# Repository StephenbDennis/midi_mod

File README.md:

# Github Pages
https://stephenbdennis.github.io/midi_mod/

# Modular USB MIDI Controller (Midi-Mod)

A **USB MIDI device** that supports up to **3 hot-swappable input modules**, configurable as **buttons**, **sliders**, or **potentiometers**.  
I was going for a compact design that allowed the user to configure their Midi-Mod device without needing firmware updates.
* Note: This is a work in progress... It's working, but there are many things that could be improved.

---

## Configure it in a browser

**[stephenbdennis.github.io/midi_mod](https://stephenbdennis.github.io/midi_mod/)**

Pick a message for every input and watch the MIDI bytes it will put on the wire. There is a preset
per module type (Buttons, Sliders, Pots), it imports a config you already have, and it can listen to
the device over Web MIDI so you can check what it is actually sending. Everything runs in the
browser; nothing is uploaded.

**Connect** pairs with the device over Bluetooth. From there **Load from device** pulls the config
that is on it right now, and **Send to device** writes `config.toml` back and applies it
immediately &mdash; no replug, and the device stays a USB MIDI interface throughout, so you can keep
playing into a DAW while you edit. Transfers are checksummed in both directions and rejected if they
do not match.

Bluetooth needs Web Bluetooth, so it is Chrome, Edge and Opera only (on Linux you may have to enable
it in `chrome://flags`). Everywhere else, Download still gives you the same `config.toml`.

---

### Project Build and Flash

Needs **ESP-IDF 5.2 or newer**. Dependencies come from `dependencies.lock`; `idf.py` fetches them
on the first build.

```
idf.py set-target esp32s3
idf.py build
idf.py -p COM<xxx> flash
idf.py -p COM<xxx> monitor
```

---

## Features

- **Up to 3 modules active at once**
- Modules can be:
  - Button Module (5 Cherry Mx buttons)
  - Slider Module (2 Linear Potentiometers)
  - Pot Module (5 Knob Potentiometers)
- Modules can be **mixed** (e.g. 3 Button Modules or 1 Button + 1 Slider + 1 Pot)
- **Every MIDI message**: notes, aftertouch, control change, program change, pitch bend, and the
  system common and real time messages
- Configurable with onboard .toml(ish) file
- BLE config service, so it can be reconfigured while it plays

---

## Module Types

Each module occupies **one slot**.  
A maximum of **3 slots** are available.

### 1. Button Module
- Defaults to a digital device when connected

### 2. Slider Module
- Defaults to an analog device when connected
- Uses dual sliders, so device 1 and 2 should have the roughly the same value. and well as 3 and 4. Device 5 is tied to ground.

### 3. Potentiometer Module
- Defaults to an analog device when connected

---

## Configuration
- The device advertises over Bluetooth LE as **MIDI-Mod** whenever it is powered. Open the
  configurator, press Connect, and pick it from the browser's device chooser. There is no config
  boot mode any more: USB is the MIDI interface full time.

- **Send to device** writes `config.toml` into the device's internal filesystem and applies it on
  the next poll tick, so a change is audible straight away.

- `reference.txt` is written to the internal filesystem on first boot. It documents the config
  format, though the same reference is on the configurator page under **Message reference**.

- If no config.toml is present the device writes the example below, so there is always something to edit.

- A line starting with `#` is a comment. Numbers are hexadecimal.

### Module Options
- press_velocity : (Optional) 0x0-0x7F : Defaults to 0x7F
  - This is the note_on/note_off message velocity. Only used with buttons
- channel 	     : (Optional) 0x0-0xF  : Defaults to 0x0
  - The channel messages are sent on. (Part of the MIDI message)
- alpha	    	 : (Optional) 0.01-0.5 : Defaults to 0.3
  - This value changes the responsivity of the input. Higher is faster, Lower is smoother but slower. Currently buttons are analog reads, so this should be pretty high when using that module
### Device Options
- device_type          : (Optional) analog,digital                 : Defaults to module type
  - Digital: triggers message_on_change on the rising edge and message_on_stop on the falling edge. 
  - Analog:  triggers message_on_change when value is changing and message_on_stop when the value is no longer changing. 
- channel              : (Optional) 0x0-0xF,inherit                : Defaults to inherit
  - Overrides the module channel for this one input. System messages ignore it.
- message_on_change    : (Optional) see Messages below             : Defaults to noop
  - The message to send when the value changes (analog) or rising edge (digital). This can be a name or a status byte
- message_on_stop      : (Optional) see Messages below             : Defaults to noop
  - The message to send when the value stops changing (analog) or falling edge (digital). This can be a name or a status byte
- data 	               : (Optional) notes,0x0-0x7F                 : Defaults to 0x0. 
  - For messages that carry a note, controller or program number this will be the value in the message. This can be a note string or a hex value. Overwritten by Manual Data
- manual_data_change_0 : (Optional) 0x0-0x7F,dev                   : Not used if not set
  - If set this will set the first data byte on a change action to this value. If dev, the value of the device is used 
- manual_data_change_1 : (Optional) 0x0-0x7F,dev                   : Not used if not set
  - If set this will set the second data byte on a change action to this value. If dev, the value of the device is used
- manual_data_stop_0   : (Optional) 0x0-0x7F,dev                   : Not used if not set
  - If set this will set the first data byte on a stop action to this value. If dev, the value of the device is used
- manual_data_stop_1   : (Optional) 0x0-0x7F,dev                   : Not used if not set
  - If set this will set the second data byte on a stop action to this value. If dev, the value of the device is used

### Messages

`input` is the live 0-127 reading of the button, slider or knob. `data` is the device's `data` option.

| Name | Status | Bytes | Data 1 | Data 2 |
| --- | --- | --- | --- | --- |
| `noop` | - | 0 | nothing is sent | |
| `note_off` | 0x80 | 3 | note (data) | velocity (press_velocity) |
| `note_on` | 0x90 | 3 | note (data) | velocity (press_velocity) |
| `poly_aftertouch` | 0xA0 | 3 | note (data) | pressure (input) |
| `cc` | 0xB0 | 3 | controller (data) | value (input) |
| `pc` | 0xC0 | 2 | program (data) | |
| `channel_aftertouch` | 0xD0 | 2 | pressure (input) | |
| `pitch_bend` | 0xE0 | 3 | bend LSB (input) | bend MSB (input) |
| `mtc_quarter_frame` | 0xF1 | 2 | time code (data) | |
| `song_position` | 0xF2 | 3 | position LSB (input) | position MSB (input) |
| `song_select` | 0xF3 | 2 | song (data) | |
| `tune_request` | 0xF6 | 1 | | |
| `clock` | 0xF8 | 1 | | |
| `start` | 0xFA | 1 | | |
| `continue` | 0xFB | 1 | | |
| `stop` | 0xFC | 1 | | |
| `active_sensing` | 0xFE | 1 | | |
| `system_reset` | 0xFF | 1 | | |

- Aliases: `control_change` = `cc`, `program_change` = `pc`, `channel_pressure` = `channel_aftertouch`, `timing_clock` = `clock`
- A raw status byte such as `0x90` works in place of a name
- Messages from 0xF1 up are system messages and ignore the channel
- `pitch_bend` and `song_position` spread the 0-127 reading across their full 14 bit range

### Notes
`C_(-1..9)` `C#_(-1..9)` `D_(-1..9)` `D#_(-1..9)` `E_(-1..9)` `F_(-1..9)` `F#_(-1..9)` `G_(-1..9)` `G#_(-1..8)` `A_(-1..8)` `A#_(-1..8)` `B_(-1..8)`

### Example
```
[module1]
channel = 0x0
press_velocity = 0x7F
alpha = 0.5
[module1.device1]
message_on_change = note_on
message_on_stop = note_off
data = C_3
[module1.device2]
message_on_change = note_on
message_on_stop = note_off
data = D_3
[module1.device3]
message_on_change = note_on
message_on_stop = note_off
data = E_3
[module1.device4]
message_on_change = start
message_on_stop = stop
[module1.device5]
message_on_change = pc
data = 0x0

[module2]
channel = 0x0
alpha = 0.3
[module2.device1]
message_on_change = cc
data = 0x1
[module2.device2]
message_on_change = cc
data = 0x7
[module2.device3]
message_on_change = cc
data = 0xA
[module2.device4]
message_on_change = pitch_bend
[module2.device5]
message_on_change = channel_aftertouch

[module3]
channel = 0x1
alpha = 0.3
[module3.device1]
message_on_change = cc
data = 0x0
[module3.device2]
message_on_change = cc
data = 0x2
[module3.device3]
message_on_change = poly_aftertouch
data = C_3
[module3.device4]
message_on_change = cc
data = 0x4
[module3.device5]
message_on_change = cc
data = 0x5
```

---

## Repo layout

| Path | What it is |
| --- | --- |
| `main/` | ESP32-S3 firmware |
| `boards/` | KiCad projects for the main board and the three module types |
| `docs/` | The web configurator, published to GitHub Pages |
| `.github/workflows/pages.yml` | Deploys `docs/` on every push to `main` |

To turn the page on, set **Settings → Pages → Source** to **GitHub Actions**. (Deploying from the
`main` branch `/docs` folder works too, and needs no workflow.)

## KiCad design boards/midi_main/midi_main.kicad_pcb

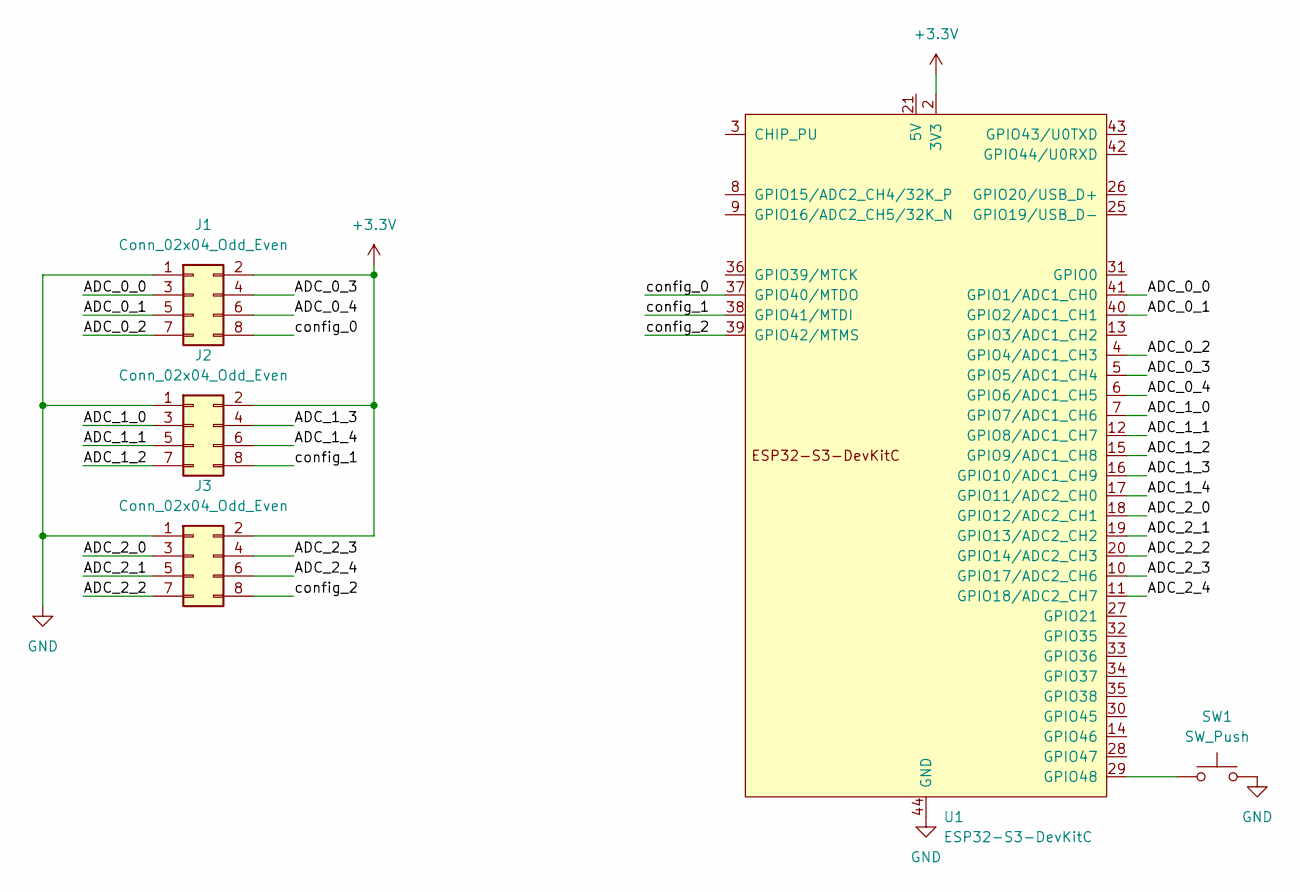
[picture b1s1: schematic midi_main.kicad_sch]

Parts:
J1, J2, J3: Conn_02x04_Odd_Even; MidiModuleOutline
SW1: SW_Push; SW_PUSH_6mm_H7.3mm
U1: ESP32-S3-DevKitC; ESP32-S3-DevKitC_Steve

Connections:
+3.3V: J1.2, J2.2, J3.2, U1.1 (3V3), U1.2 (3V3)
/ADC_0_0: J1.3, U1.41 (GPIO1/ADC1_CH0)
/ADC_0_1: J1.5, U1.40 (GPIO2/ADC1_CH1)
/ADC_0_2: J1.7, U1.4 (GPIO4/ADC1_CH3)
/ADC_0_3: J1.4, U1.5 (GPIO5/ADC1_CH4)
/ADC_0_4: J1.6, U1.6 (GPIO6/ADC1_CH5)
/ADC_1_0: J2.3, U1.7 (GPIO7/ADC1_CH6)
/ADC_1_1: J2.5, U1.12 (GPIO8/ADC1_CH7)
/ADC_1_2: J2.7, U1.15 (GPIO9/ADC1_CH8)
/ADC_1_3: J2.4, U1.16 (GPIO10/ADC1_CH9)
/ADC_1_4: J2.6, U1.17 (GPIO11/ADC2_CH0)
/ADC_2_0: J3.3, U1.18 (GPIO12/ADC2_CH1)
/ADC_2_1: J3.5, U1.19 (GPIO13/ADC2_CH2)
/ADC_2_2: J3.7, U1.20 (GPIO14/ADC2_CH3)
/ADC_2_3: J3.4, U1.10 (GPIO17/ADC2_CH6)
/ADC_2_4: J3.6, U1.11 (GPIO18/ADC2_CH7)
/config_0: J1.8, U1.37 (GPIO40/MTDO)
/config_1: J2.8, U1.38 (GPIO41/MTDI)
/config_2: J3.8, U1.39 (GPIO42/MTMS)
GND: J1.1, J2.1, J3.1, SW1.2, U1.22 (GND), U1.23 (GND), U1.24 (GND), U1.44 (GND)
unnamed: SW1.1, U1.29 (GPIO48)

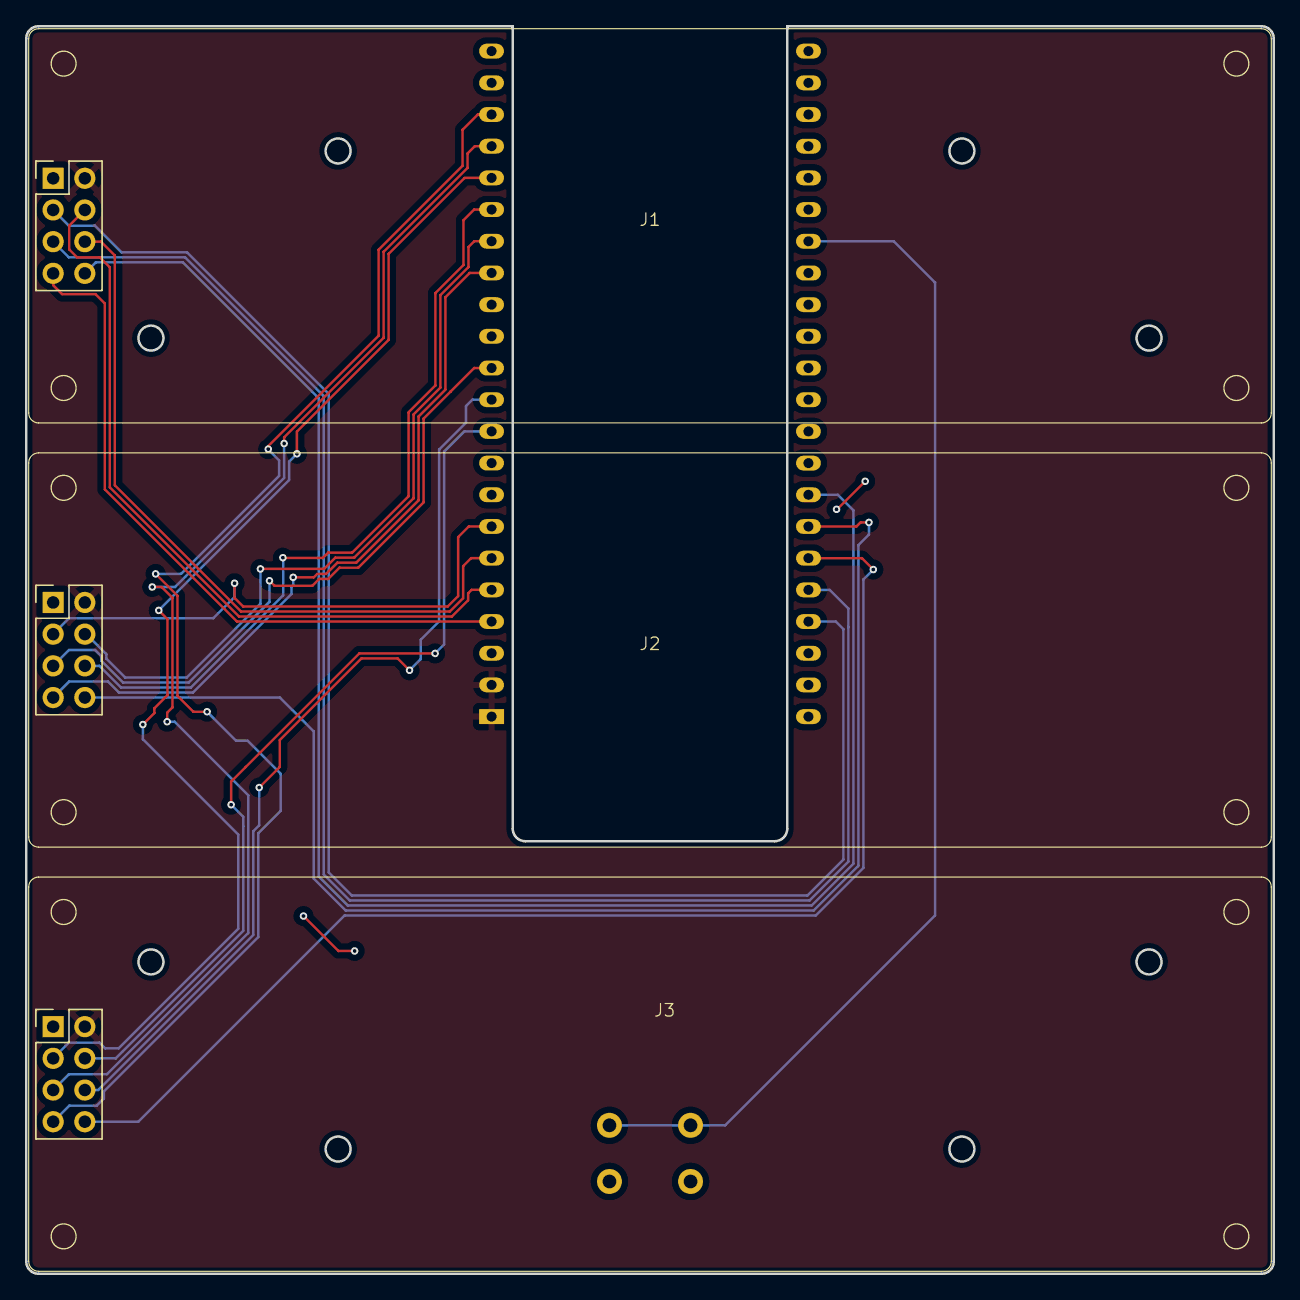
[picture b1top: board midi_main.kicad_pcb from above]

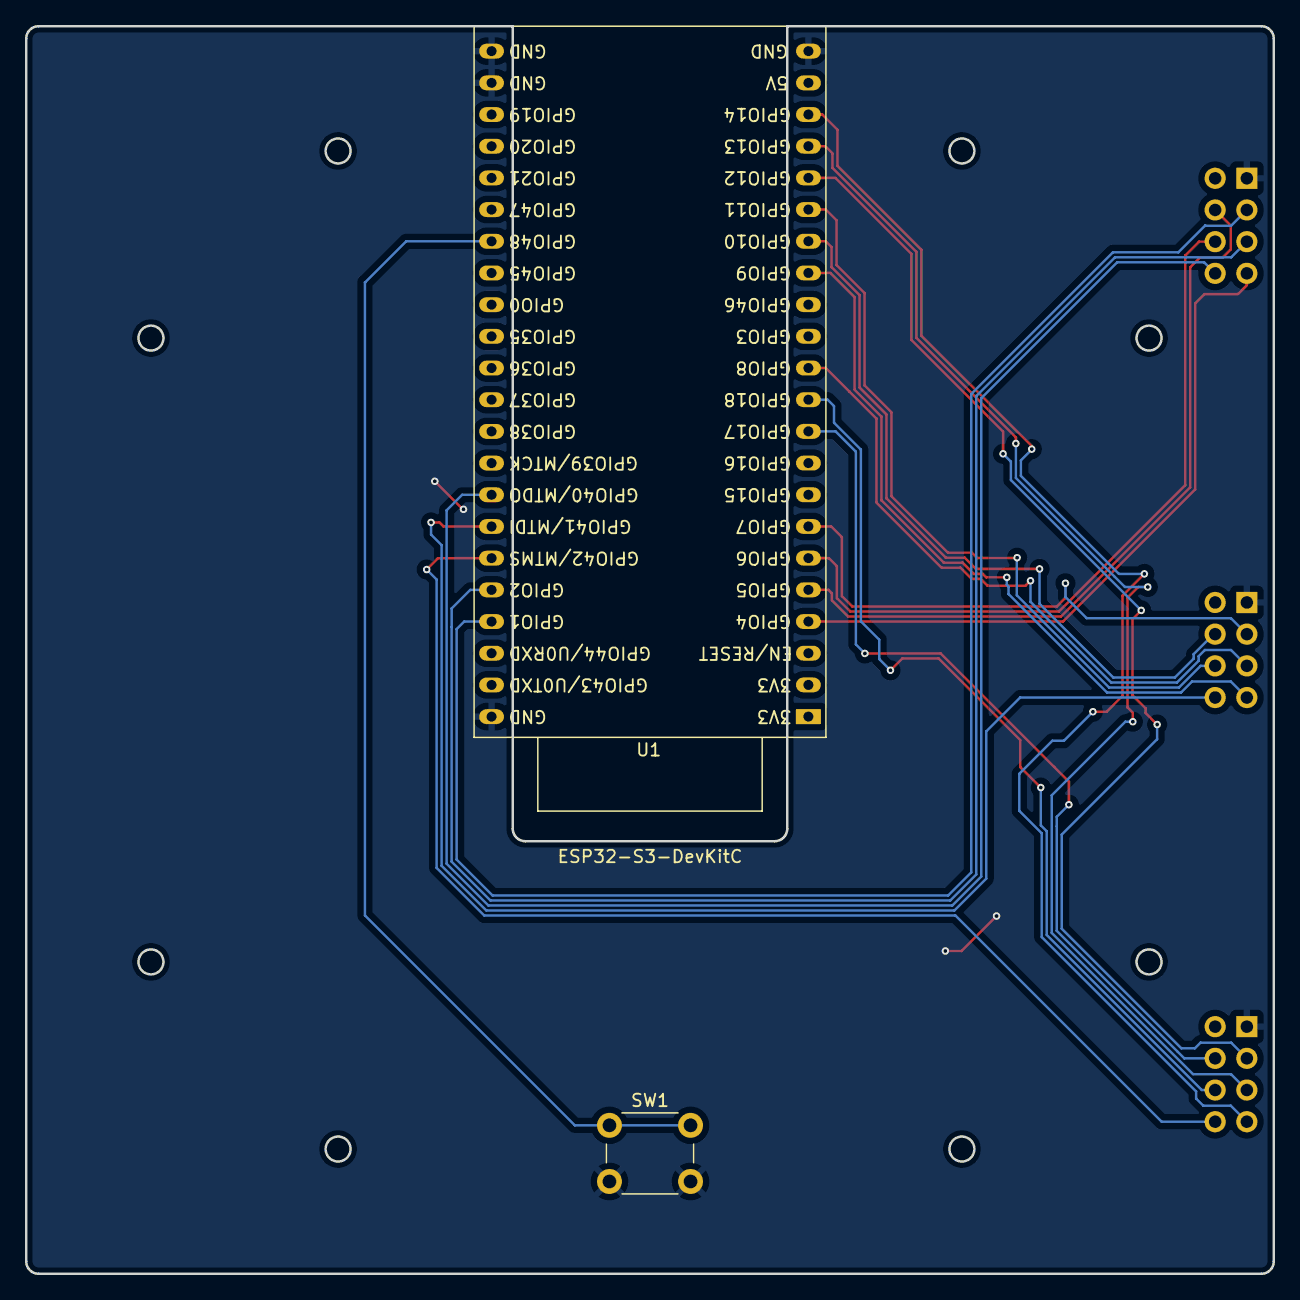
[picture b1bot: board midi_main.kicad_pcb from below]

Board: 2 copper layers, 100.0 x 100.0 mm, 5 parts (2 on the bottom side), 21 nets.

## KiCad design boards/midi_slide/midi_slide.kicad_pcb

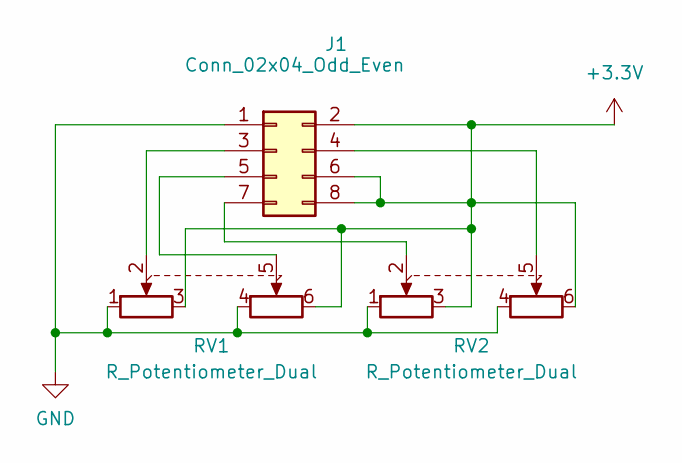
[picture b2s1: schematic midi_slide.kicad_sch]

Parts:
J1: Conn_02x04_Odd_Even; MidiModuleBase
RV1, RV2: R_Potentiometer_Dual; PS60M-0MC2BR10KN

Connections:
+3.3V: J1.2, J1.6, J1.8, RV1.3, RV1.6, RV2.3, RV2.6
GND: J1.1, RV1.1, RV1.4, RV2.1, RV2.4
unnamed: J1.3, RV1.2
unnamed: J1.4, RV2.5
unnamed: J1.5, RV1.5
unnamed: J1.7, RV2.2

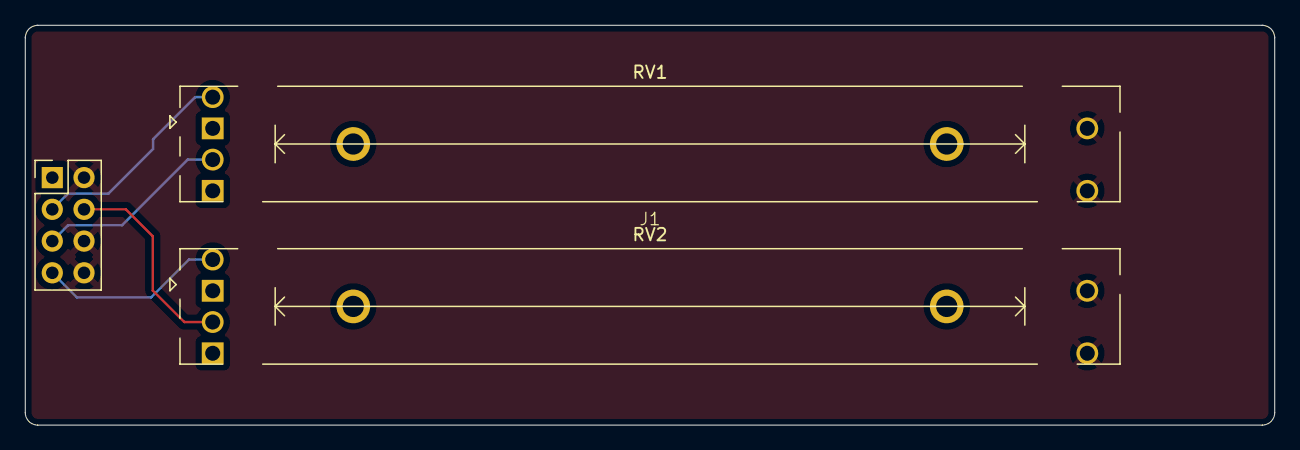
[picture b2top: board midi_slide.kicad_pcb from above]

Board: 2 copper layers, 100.0 x 32.0 mm, 3 parts (0 on the bottom side), 6 nets.

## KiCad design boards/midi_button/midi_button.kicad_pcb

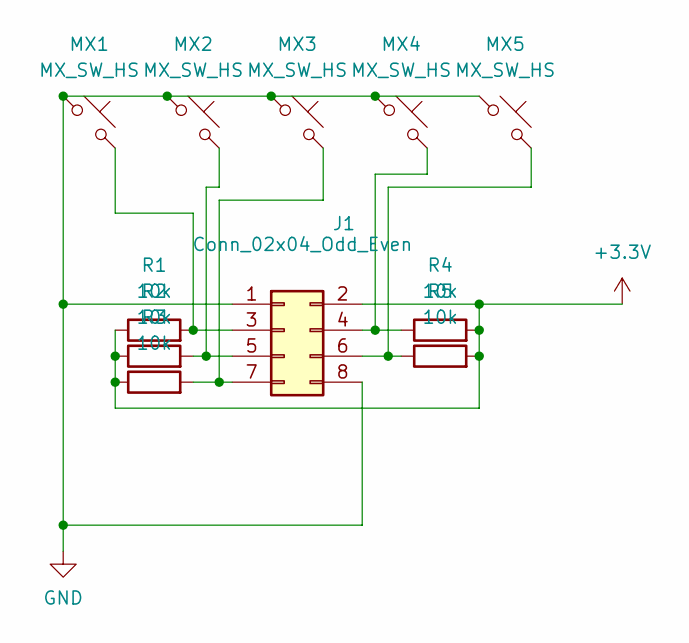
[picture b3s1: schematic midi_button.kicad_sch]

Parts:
J1: Conn_02x04_Odd_Even; MidiModuleBase
MX1, MX2, MX3, MX4, MX5: MX_SW_HS; SW_MX_HS_CPG151101S11_1u
R1, R2, R3, R4, R5: 10k; R_Axial_DIN0207_L6.3mm_D2.5mm_P7.62mm_Horizontal

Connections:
+3.3V: J1.2, R1.1, R2.1, R3.1, R4.2, R5.2
GND: J1.1, J1.8, MX1.1, MX2.1, MX3.1, MX4.1, MX5.1
unnamed: J1.3, MX1.2, R1.2
unnamed: J1.4, MX4.2, R4.1
unnamed: J1.5, MX2.2, R2.2
unnamed: J1.6, MX5.2, R5.1
unnamed: J1.7, MX3.2, R3.2

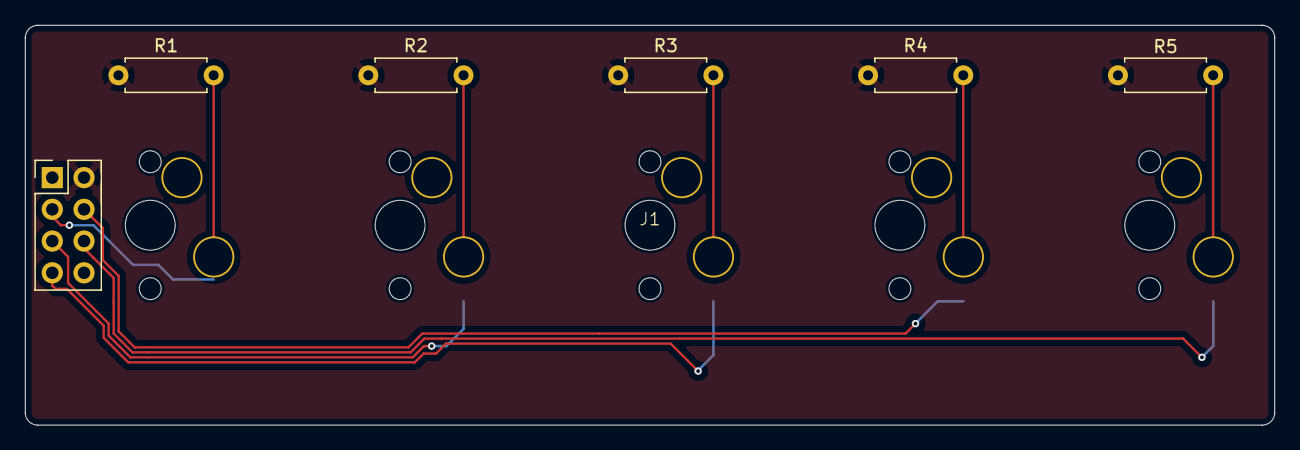
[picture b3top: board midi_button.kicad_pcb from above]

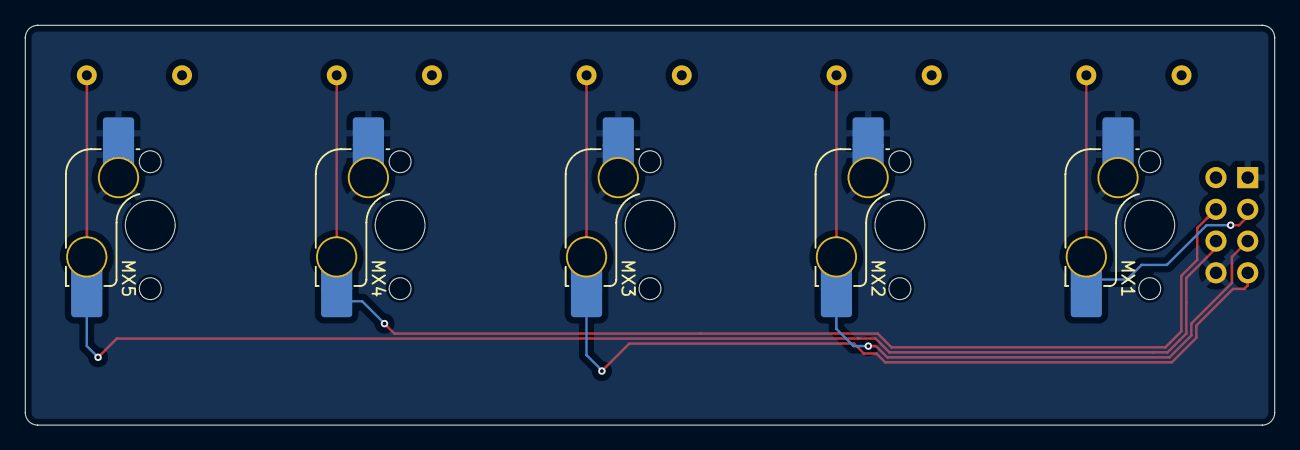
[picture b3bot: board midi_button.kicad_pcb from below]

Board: 2 copper layers, 100.0 x 32.0 mm, 11 parts (5 on the bottom side), 7 nets.

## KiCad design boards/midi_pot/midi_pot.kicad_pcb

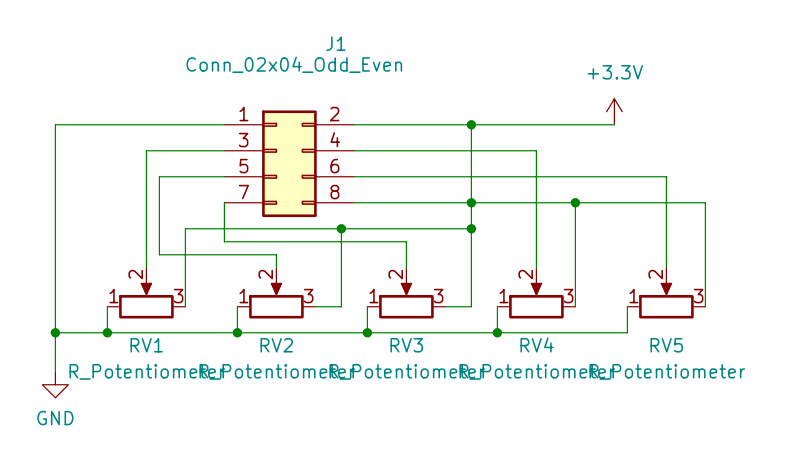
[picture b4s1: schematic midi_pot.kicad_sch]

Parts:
J1: Conn_02x04_Odd_Even; MidiModuleBase
RV1, RV2, RV3, RV4, RV5: R_Potentiometer; Potentiometer_Alpha_RD901F-40-00D_Single_Vertical_CENTER

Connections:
+3.3V: J1.2, J1.8, RV1.3, RV2.3, RV3.3, RV4.3, RV5.3
GND: J1.1, RV1.1, RV2.1, RV3.1, RV4.1, RV5.1
unnamed: J1.3, RV1.2
unnamed: J1.4, RV4.2
unnamed: J1.5, RV2.2
unnamed: J1.6, RV5.2
unnamed: J1.7, RV3.2

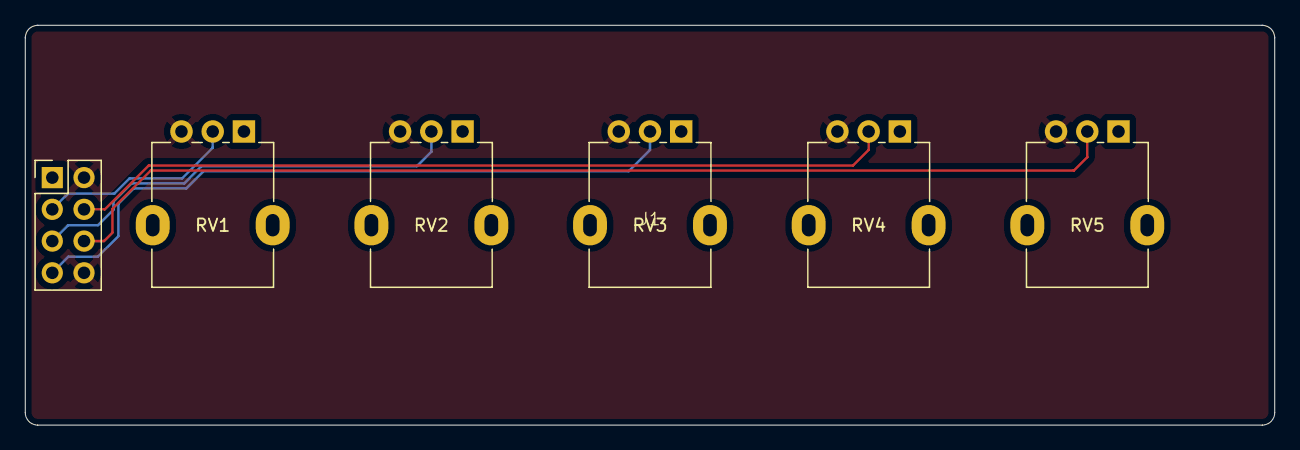
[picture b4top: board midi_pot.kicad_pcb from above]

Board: 2 copper layers, 100.0 x 32.0 mm, 6 parts (0 on the bottom side), 7 nets.

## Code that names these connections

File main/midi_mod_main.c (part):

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// --- Pin Mapping ---
// Common
#define GPIO_LAYER_SELECT       GPIO_NUM_38     // GPIO38
#define MAIN_LED                GPIO_NUM_48     // GPIO48

// Device 1
#define ADC_0_0                 ADC_CHANNEL_0   // GPIO1
#define ADC_0_1                 ADC_CHANNEL_1   // GPIO2
#define ADC_0_2                 ADC_CHANNEL_3   // GPIO4
#define ADC_0_3                 ADC_CHANNEL_4   // GPIO5
#define ADC_0_4                 ADC_CHANNEL_5   // GPIO6
#define GPIO_DEVICE_1_SELECT    GPIO_NUM_40     // GPIO40

// Device 2
#define ADC_1_0                 ADC_CHANNEL_6   // GPIO7
#define ADC_1_1                 ADC_CHANNEL_7   // GPIO8
#define ADC_1_2                 ADC_CHANNEL_8   // GPIO9
#define ADC_1_3                 ADC_CHANNEL_9   // GPIO10
#define ADC_1_4                 ADC_CHANNEL_0   // GPIO11
#define GPIO_DEVICE_2_SELECT    GPIO_NUM_41     // GPIO41

// Device 3
#define ADC_2_0                 ADC_CHANNEL_1   // GPIO12
#define ADC_2_1                 ADC_CHANNEL_2   // GPIO13
#define ADC_2_2                 ADC_CHANNEL_3   // GPIO14
#define ADC_2_3                 ADC_CHANNEL_6   // GPIO17
#define ADC_2_4                 ADC_CHANNEL_7   // GPIO18
#define GPIO_DEVICE_3_SELECT    GPIO_NUM_42     // GPIO42

// TinyUSB Settings
#define TUSB_DESCRIPTOR_TOTAL_LEN (TUD_CONFIG_DESC_LEN + CFG_TUD_MIDI * TUD_MIDI_DESC_LEN)
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
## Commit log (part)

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2025-10-17 Add boards
2025-12-09 Create Midi Manager
2025-12-12 msc working
2025-12-23 Create LICENSE
2025-12-23 Working
